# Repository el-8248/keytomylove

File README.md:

# keytomylove
a macropad design for the **ysws** project [KEEB](https://keeb.hackclub.com)

this project is a project for teens following the **you ship we ship** model

In exchange for my hard work and learning on this project, the Hack Club non-profit is going to fund what it takes to bring it to life

## Process
### 1 -- the initial design process (2 hrs)
I originally...(wip)

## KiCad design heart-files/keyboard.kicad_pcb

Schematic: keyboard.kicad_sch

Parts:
D_0, D_1, D_2, D_3, D_4, D_5, D_6, D_7, D_8, D_9, D_10, D_11, D_12, D_13, D_14, D_15, D_16, D_17, D_18, D_19, D_20, D_21, D_22, D_23, D_24, D_25, D_26, D_27, D_28, D_29, D_30, D_31, D_32, D_33, D_34, D_35, D_36, D_37, D_38, D_39, D_40, D_41, D_42, D_43, D_44, D_45, D_46, D_47, D_48, D_49, D_50, D_51, D_52, D_53, D_54, D_55, D_56, D_57, D_58, D_59, D_60, D_61, D_62, D_63, D_64, D_65, D_66, D_67, D_68, D_69, D_70, D_71, D_72, D_73, D_74, D_75, D_76, D_77, D_78, D_79, D_80, D_81, D_82, D_83: D; D_SOD-123
K_0, K_1, K_2, K_3, K_4, K_5, K_6, K_7, K_8, K_9, K_10, K_11, K_12, K_13, K_14, K_15, K_16, K_17, K_18, K_19, K_20, K_21, K_22, K_23, K_24, K_25, K_26, K_27, K_28, K_30, K_32, K_33, K_34, K_35, K_36, K_37, K_38, K_39, K_40, K_41, K_42, K_43, K_45, K_47, K_48, K_49, K_50, K_51, K_52, K_53, K_54, K_55, K_56, K_57, K_59, K_61, K_62, K_63, K_64, K_65, K_66, K_67, K_68, K_69, K_70, K_72, K_73, K_78, K_79, K_80, K_81, K_82, K_83: KEYSW; MX-1U-NoLED
K_29: KEYSW; MX-2U-NoLED
K_31, K_44: KEYSW; MX-1.5U-NoLED
K_46, K_71: KEYSW; MX-1.75U-NoLED
K_58, K_60: KEYSW; MX-2.25U-NoLED
K_74, K_75, K_76: KEYSW; MX-1.25U-NoLED
K_77: KEYSW; MX-6.25U-NoLED

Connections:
unnamed: D_0.2 (A), K_0.2
unnamed: D_1.2 (A), K_1.2
unnamed: D_2.2 (A), K_2.2
unnamed: D_3.2 (A), K_3.2
unnamed: D_4.2 (A), K_4.2
unnamed: D_5.2 (A), K_5.2
unnamed: D_6.2 (A), K_6.2
unnamed: D_7.2 (A), K_7.2
unnamed: D_8.2 (A), K_8.2
unnamed: D_9.2 (A), K_9.2
unnamed: D_10.2 (A), K_10.2
unnamed: D_11.2 (A), K_11.2
unnamed: D_12.2 (A), K_12.2
unnamed: D_13.2 (A), K_13.2
unnamed: D_14.2 (A), K_14.2
unnamed: D_15.2 (A), K_15.2
unnamed: D_16.2 (A), K_16.2
unnamed: D_17.2 (A), K_17.2
unnamed: D_18.2 (A), K_18.2
unnamed: D_19.2 (A), K_19.2
unnamed: D_20.2 (A), K_20.2
unnamed: D_21.2 (A), K_21.2
unnamed: D_22.2 (A), K_22.2
unnamed: D_23.2 (A), K_23.2
unnamed: D_24.2 (A), K_24.2
unnamed: D_25.2 (A), K_25.2
unnamed: D_26.2 (A), K_26.2
unnamed: D_27.2 (A), K_27.2
unnamed: D_28.2 (A), K_28.2
unnamed: D_29.2 (A), K_29.2
unnamed: D_30.2 (A), K_30.2
unnamed: D_31.2 (A), K_31.2
unnamed: D_32.2 (A), K_32.2
unnamed: D_33.2 (A), K_33.2
unnamed: D_34.2 (A), K_34.2
unnamed: D_35.2 (A), K_35.2
unnamed: D_36.2 (A), K_36.2
unnamed: D_37.2 (A), K_37.2
unnamed: D_38.2 (A), K_38.2
unnamed: D_39.2 (A), K_39.2
unnamed: D_40.2 (A), K_40.2
unnamed: D_41.2 (A), K_41.2
unnamed: D_42.2 (A), K_42.2
unnamed: D_43.2 (A), K_43.2
unnamed: D_44.2 (A), K_44.2
unnamed: D_45.2 (A), K_45.2
unnamed: D_46.2 (A), K_46.2
unnamed: D_47.2 (A), K_47.2
unnamed: D_48.2 (A), K_48.2
unnamed: D_49.2 (A), K_49.2
unnamed: D_50.2 (A), K_50.2
unnamed: D_51.2 (A), K_51.2
unnamed: D_52.2 (A), K_52.2
unnamed: D_53.2 (A), K_53.2
unnamed: D_54.2 (A), K_54.2
unnamed: D_55.2 (A), K_55.2
unnamed: D_56.2 (A), K_56.2
unnamed: D_57.2 (A), K_57.2
unnamed: D_58.2 (A), K_58.2
unnamed: D_59.2 (A), K_59.2
unnamed: D_60.2 (A), K_60.2
unnamed: D_61.2 (A), K_61.2
unnamed: D_62.2 (A), K_62.2
unnamed: D_63.2 (A), K_63.2
unnamed: D_64.2 (A), K_64.2
unnamed: D_65.2 (A), K_65.2
unnamed: D_66.2 (A), K_66.2
unnamed: D_67.2 (A), K_67.2
unnamed: D_68.2 (A), K_68.2
unnamed: D_69.2 (A), K_69.2
unnamed: D_70.2 (A), K_70.2
unnamed: D_71.2 (A), K_71.2
unnamed: D_72.2 (A), K_72.2
unnamed: D_73.2 (A), K_73.2
unnamed: D_74.2 (A), K_74.2
unnamed: D_75.2 (A), K_75.2
unnamed: D_76.2 (A), K_76.2
unnamed: D_77.2 (A), K_77.2
unnamed: D_78.2 (A), K_78.2
unnamed: D_79.2 (A), K_79.2
unnamed: D_80.2 (A), K_80.2
unnamed: D_81.2 (A), K_81.2
unnamed: D_82.2 (A), K_82.2
unnamed: D_83.2 (A), K_83.2
col0: K_0.1, K_16.1, K_31.1, K_46.1, K_74.1
col1: K_1.1, K_17.1, K_60.1, K_75.1
col2: K_2.1, K_18.1, K_32.1, K_47.1, K_61.1
col3: K_3.1, K_19.1, K_33.1, K_48.1, K_62.1, K_76.1
col4: K_4.1, K_20.1, K_34.1, K_49.1, K_63.1
col5: K_5.1, K_21.1, K_35.1, K_50.1, K_64.1
col6: K_6.1, K_22.1, K_36.1, K_51.1, K_65.1, K_77.1
col7: K_7.1, K_23.1, K_37.1, K_52.1, K_66.1
col8: K_8.1, K_24.1, K_38.1, K_53.1, K_67.1
col9: K_9.1, K_25.1, K_39.1, K_54.1, K_68.1
col10: K_10.1, K_26.1, K_40.1, K_55.1, K_69.1, K_78.1
col11: K_11.1, K_27.1, K_41.1, K_56.1, K_70.1, K_79.1
col12: K_12.1, K_28.1, K_42.1, K_57.1, K_80.1
col13: K_13.1, K_43.1, K_58.1, K_71.1, K_81.1
col14: K_14.1, K_29.1, K_44.1, K_72.1, K_82.1
col15: K_15.1, K_30.1, K_45.1, K_59.1, K_73.1, K_83.1
row0: D_0.1 (K), D_1.1 (K), D_2.1 (K), D_3.1 (K), D_4.1 (K), D_5.1 (K), D_6.1 (K), D_7.1 (K), D_8.1 (K), D_9.1 (K), D_10.1 (K), D_11.1 (K), D_12.1 (K), D_13.1 (K), D_14.1 (K), D_15.1 (K)
row1: D_16.1 (K), D_17.1 (K), D_18.1 (K), D_19.1 (K), D_20.1 (K), D_21.1 (K), D_22.1 (K), D_23.1 (K), D_24.1 (K), D_25.1 (K), D_26.1 (K), D_27.1 (K), D_28.1 (K), D_29.1 (K), D_30.1 (K)
row2: D_31.1 (K), D_32.1 (K), D_33.1 (K), D_34.1 (K), D_35.1 (K), D_36.1 (K), D_37.1 (K), D_38.1 (K), D_39.1 (K), D_40.1 (K), D_41.1 (K), D_42.1 (K), D_43.1 (K), D_44.1 (K), D_45.1 (K)
row3: D_46.1 (K), D_47.1 (K), D_48.1 (K), D_49.1 (K), D_50.1 (K), D_51.1 (K), D_52.1 (K), D_53.1 (K), D_54.1 (K), D_55.1 (K), D_56.1 (K), D_57.1 (K), D_58.1 (K), D_59.1 (K)
row4: D_60.1 (K), D_61.1 (K), D_62.1 (K), D_63.1 (K), D_64.1 (K), D_65.1 (K), D_66.1 (K), D_67.1 (K), D_68.1 (K), D_69.1 (K), D_70.1 (K), D_71.1 (K), D_72.1 (K), D_73.1 (K)
row5: D_74.1 (K), D_75.1 (K), D_76.1 (K), D_77.1 (K), D_78.1 (K), D_79.1 (K), D_80.1 (K), D_81.1 (K), D_82.1 (K), D_83.1 (K)

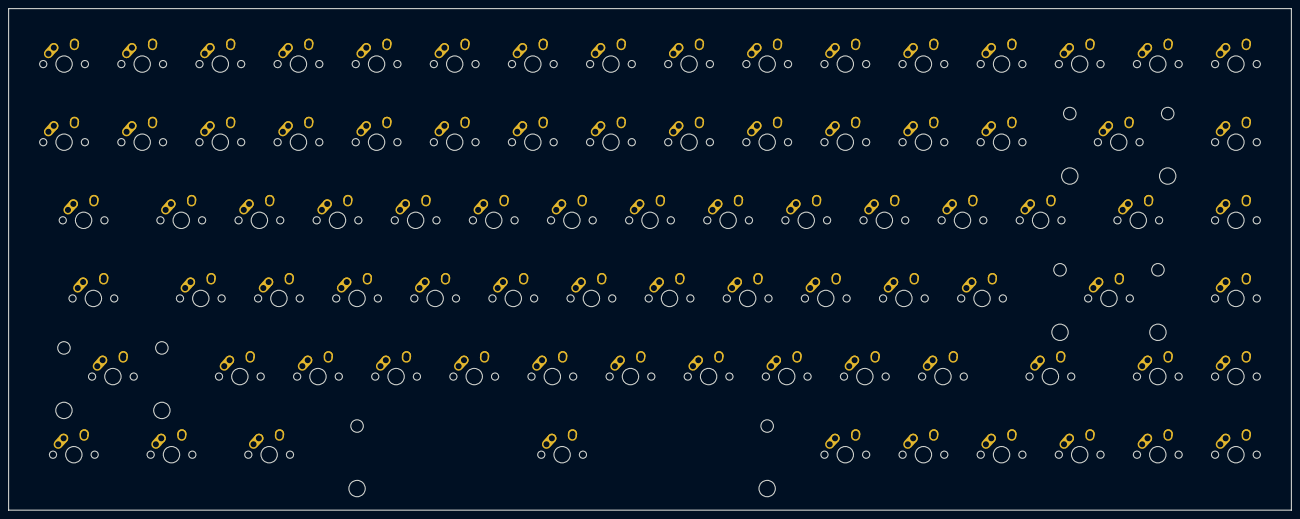
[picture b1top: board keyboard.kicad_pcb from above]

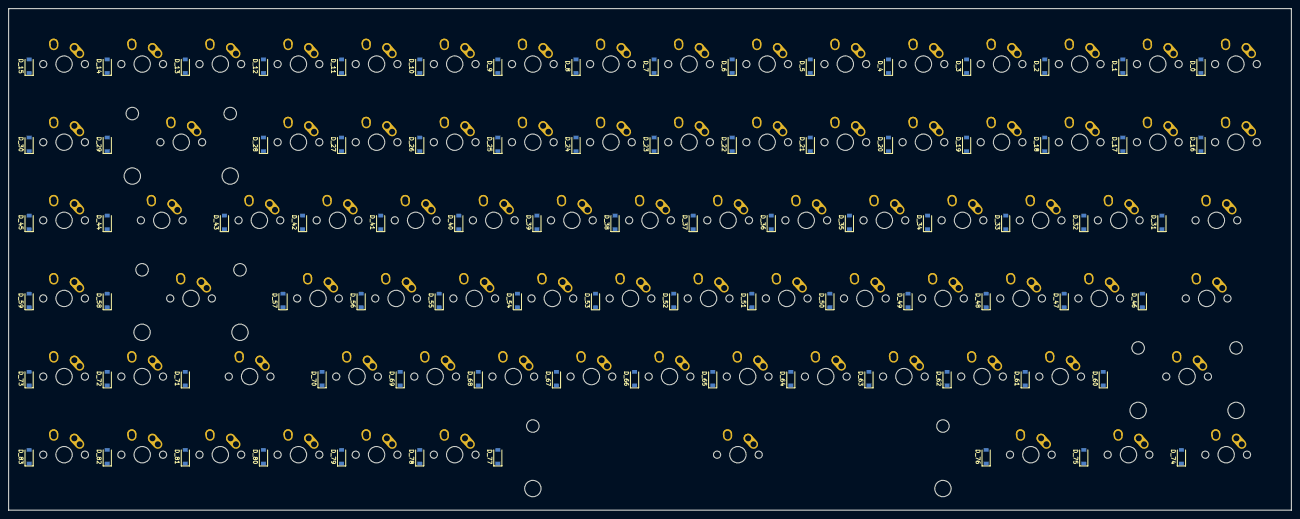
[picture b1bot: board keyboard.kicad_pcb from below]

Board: 2 copper layers, 312.8 x 122.3 mm, 168 parts (84 on the bottom side), 106 nets, no tracks yet.

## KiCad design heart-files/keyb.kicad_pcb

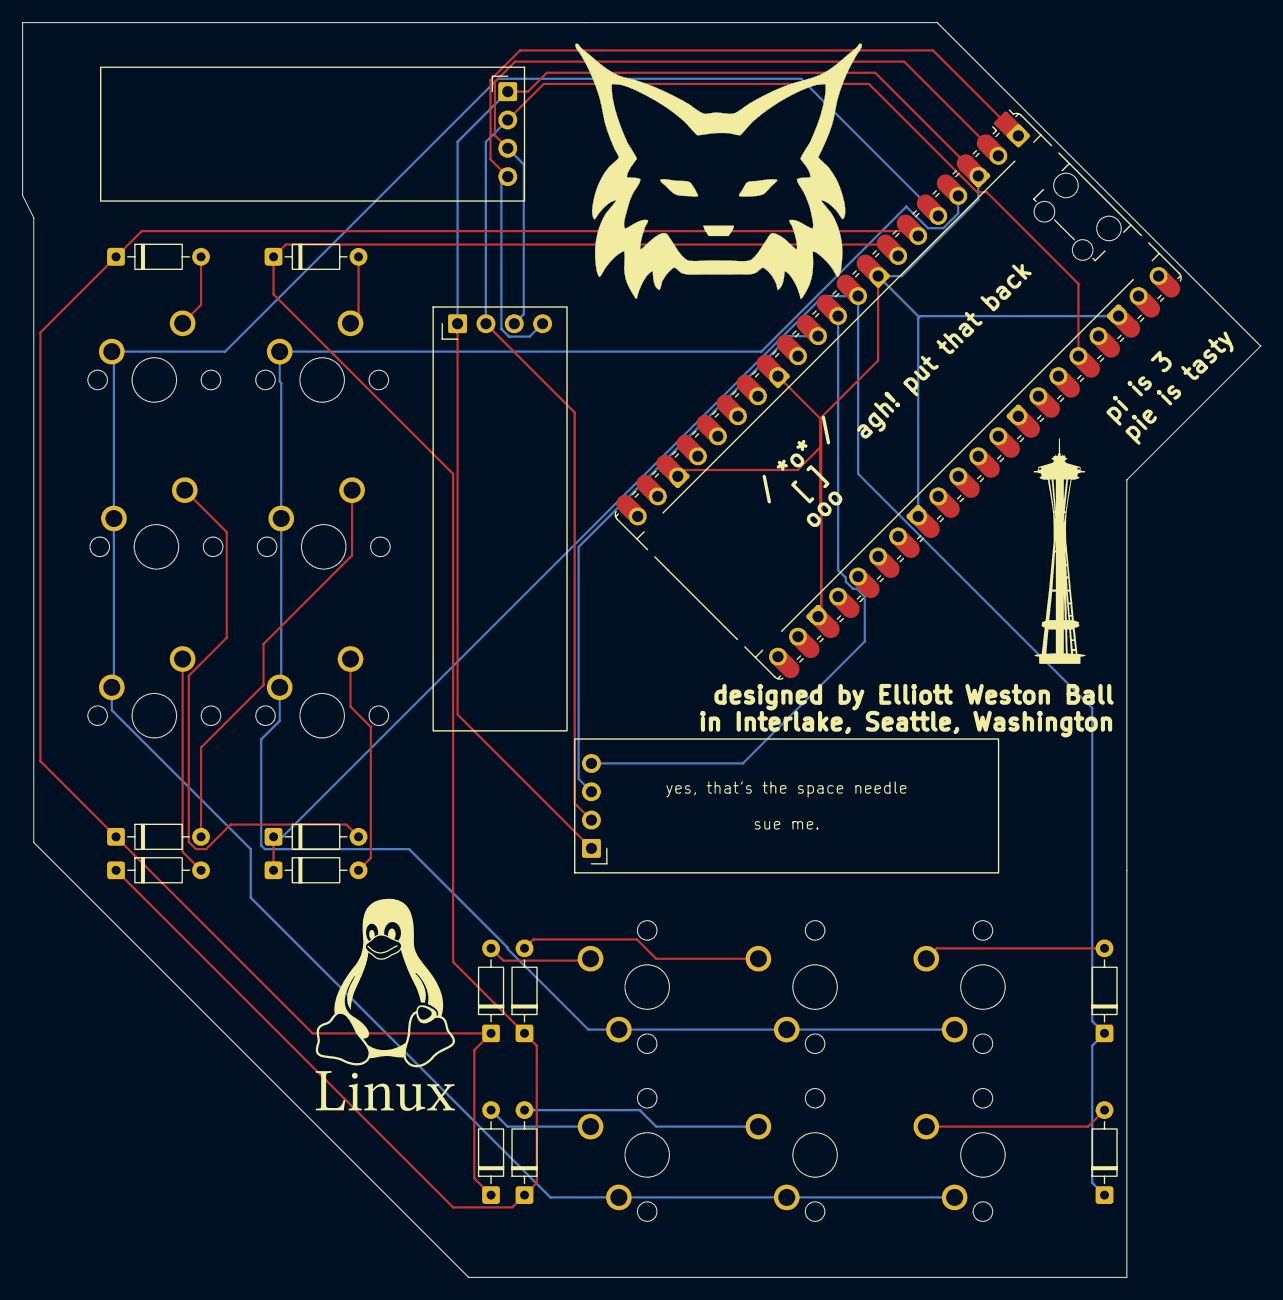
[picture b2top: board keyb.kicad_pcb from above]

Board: 2 copper layers, 111.0 x 112.5 mm, 28 parts (0 on the bottom side), 23 nets.

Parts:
A1: RaspberryPi_Pico; RaspberryPi_Pico_Common_Unspecified
D1, D2, D3, D4, D5, D6, D7, D8, D9, D10, D11, D12: 1N4148; D_DO-35_SOD27_P7.62mm_Horizontal
SW1, SW2, SW3, SW4, SW5, SW6, SW7, SW8, SW9, SW10, SW11, SW12: SW_Push; SW_MX_1u
U1, U1#2, U2: ER_OLEDM0.91_1x-I2C

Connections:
unnamed: A1.36 (3V3), U1.2 (VCC), U1#2.2 (VCC), U2.2 (VCC)
unnamed: A1.1 (GPIO0), U1.4 (SDA), U1#2.4 (SDA)
unnamed: A1.2 (GPIO1), U1.3 (SCL), U1#2.3 (SCL)
unnamed: A1.4 (GPIO2), SW2.1, SW3.1, SW6.1, SW7.1, SW8.1, SW9.1
unnamed: A1.5 (GPIO3), SW1.1, SW4.1, SW5.1, SW10.1, SW11.1, SW12.1
unnamed: A1.6 (GPIO4), D1.1 (K), D3.1 (K), D7.1 (K), D10.1 (K)
unnamed: A1.7 (GPIO5), D2.1 (K), D5.1 (K), D8.1 (K), D11.1 (K)
unnamed: A1.9 (GPIO6), D4.1 (K), D6.1 (K), D9.1 (K), D12.1 (K)
unnamed: A1.10 (GPIO7), U2.4 (SDA)
unnamed: A1.11 (GPIO8), U2.3 (SCL)
unnamed: D1.2 (A), SW1.2
unnamed: D3.2 (A), SW3.2
unnamed: D5.2 (A), SW5.2
unnamed: D2.2 (A), SW2.2
unnamed: D4.2 (A), SW4.2
unnamed: D6.2 (A), SW6.2
unnamed: D10.2 (A), SW10.2
unnamed: D11.2 (A), SW11.2
unnamed: D12.2 (A), SW12.2
unnamed: D7.2 (A), SW7.2
unnamed: D8.2 (A), SW8.2
unnamed: D9.2 (A), SW9.2
unnamed: A1.3 (GND), A1.8 (GND), A1.13 (GND), A1.18 (GND), A1.23 (GND), A1.28 (GND), A1.38 (GND), U1.1 (GND), U1#2.1 (GND), U2.1 (GND)

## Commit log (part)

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2026-05-28 finished pcb, next is to review, document, push and submit
